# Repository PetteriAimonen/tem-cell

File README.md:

# Custom built TEM cell for EMC measurements

This repository contains FreeCAD and KiCad design files for a [TEM cell](https://en.wikipedia.org/wiki/TEM_cell)
with integrated [LISN](https://en.wikipedia.org/wiki/Line_Impedance_Stabilization_Network).

When combined with a spectrum analyzer, it can be used for EMC pretest measurements.

More construction details are available in [my blog article](http://essentialscrap.com/tem_cell/).

## TEM cell structure

The TEM cell consists of three conductive layers: shield on the top and bottom, and septum in the middle.
The width and spacing of the conductors determines the [characteristic impedance](https://en.wikipedia.org/wiki/Characteristic_impedance) of the transmission line.
The default dimensions are designed for an impedance of 50 ohms, matching most measurement equipment.

Any non-magnetic metal can be used for the construction.
The default thickness of 1.6 mm is set for commonly available PCB material.

Coaxial connectors are mounted at each end of the cell.
In normal operation one end is terminated with a 50 ohm resistor
and the other end is connected to spectrum analyzer or signal generator.

## Dimensions

The classic source for custom TEM cell builds is [Do-it-Yourself Fabrication of an Open TEM Cell for EMC Pre-compliance](http://eagle.chaosproject.com/sandbox/acstrial/newsletters/summer08/pp2.pdf) by Sandeep M. Satav et al, 2008. It provides the formula for characteristic impedance Z0 of the cell. Goal is to select dimensions so that Z0 equals 50 ohms, to facilitate connection to measurement instruments.

$$ Z_0 = \frac{94.15 \Omega}{\sqrt{\epsilon_r} \cdot \left[ \frac{w}{2d(1 - \frac{t}{2d})} + \frac{C_f}{0.0885 \cdot \epsilon_r} \right] } $$

For air as insulator (εr = 1) and thin material (t → 0), this can be simplified to:

$$ Z_0 = \frac{94.15 \Omega}{\frac{w}{2d} + \frac{C_f}{0.0885}} $$

with the parameters:

* **w**: Width of the septum
* **d**: Distance between septum and shield
* **Cf**: Fringe capacitance

The paper further provides value 0.053 pF/cm for the fringe capacitance, based
on earlier paper [Generation of Standard EM Fields Using TEM Transmission Cells](https://www.ieee.li/pdf/essay/generation_of_standard_em_fields_using_tem_transmission_cells.pdf) by Myron L. Crawford, 1974. However Satav's paper describes an open TEM cell (with two walls), while Crawford's paper describes a closed TEM cell (with four walls).

Open TEM cell dimensions calculated based on Cf = 0.053 result in a characteristic impedance 1.7 times higher than expected. Using scale models, I have determined that Cf = 0.03 is closer to the correct value for open TEM cells. Relative width of shields and septum affects this value and also uniformity of the electromagnetic field, but optimal configuration is yet unknown.

## Integrated LISN

[(LISN schematic)](lisn/images/lisn.pdf)

Optionally a LISN can be mounted on the outside of the TEM cell.
This is useful for providing a filtered power supply to the device being tested and for measuring conducted emissions.

The LISN is a nominally 50 µH design loosely following CISPR 16 standard, providing 50 ohm impedance to DUT.
It is suitable for pretesting use for DC-supplied devices with most EMC standards.

The LISN includes integrated DC block and clamping diodes to limit output to ±0.4 Vpk.
Attenuation at the output port is 10 dB.
A slide switch selects between common mode and differential mode measurement.

The LISN maximum current is determined by inductor selection and maximum voltage by capacitor ratings.
With the listed parts, maximum output current is 1.5 A and voltage 100 VDC.

## 3D printed support blocks and LISN enclosure

Correct distance between TEM cell shields and septum is maintained by side support blocks.
These should be printed at a low infill ration (5% recommended) to reduce their effect on the dielectric constant.

LISN enclosure is designed to mount on the tapered section.
Two binding posts go through the shield to provide a connection on the inside of the cell.
Banana jacks and SMA connector are used for connecting a power supply and spectrum analyzer.

## Parametric design

The design in `OpenTEMCell.FCStd` is a [FreeCAD](https://www.freecad.org/) parametric design file.
The critical dimensions can be modified in spreadsheet form and the 3D model will update to match.

One possible design is provided as generated files in subdirectory [Model_L500mm_W350mm_H200mm](Model_L500mm_W350mm_H200mm).

## Part recommendations

Wide variety of materials can be used for the construction.
I have listed below the materials I have used to construct the Model_L500mm_W350mm_H200mm version:

**TEM cell:**

|Item|Count|
|--|--|
| [FR4 PCB material, one sided, 610x457mm](https://www.tme.eu/fi/en/details/lam457x610e1.5/one-layer-laminates/) | 3 pcs |
| [Square flange SMA connector](https://www.tme.eu/fi/en/details/rf2-155-t-00-50-g/sma-smb-smc-connectors/adam-tech/) | 2 pcs |
| [SMA terminator](https://www.tme.eu/fi/en/details/132360/sma-smb-smc-connectors/amphenol-rf/) | 1 pcs |

**LISN:**

|Item|Count|
|--|--|
|Binding posts [CL1572](https://www.tme.eu/en/details/cl1572/4mm-banana-sockets/cliff/) (red) and [CL1575](https://www.tme.eu/en/details/cl1575/4mm-banana-sockets/cliff/) (black) | 2 pcs total |
| Banana connectors [108-0902-001](https://www.digikey.fi/en/products/detail/cinch-connectivity-solutions-johnson/108-0902-001/5929) (red) and [108-0903-001](https://www.digikey.fi/en/products/detail/cinch-connectivity-solutions-johnson/108-0903-001/5930) (black) | 2 pcs total |
| [SMA connector, edge mount](https://www.tme.eu/en/details/rf2145at1750ghdw/sma-smb-smc-connectors/adam-tech/rf2-145a-t-17-50-g-hdw/) | 1 pcs |
| [9 mm long M3 standoffs](https://www.tme.eu/en/details/tff-m3x9_dr113/metal-spacers/dremec/113x09/) | 2 pcs |
| [5 mm long M3 standoffs](https://www.tme.eu/en/details/tfm-m3x5_dr223/metal-spacers/dremec/223x05/) | 2 pcs |
| M3 countersunk screws | 2 pcs |
| [Parts listed in PCB BOM](lisn/gerbers/lisn-BOM.csv) | |

## Correlation to far-field measurements

[Spreadsheet](Model_L500mm_W350mm_H200mm/CorrectionFactors.ods) is provided for calculating correction factor for converting TEM cell measurements in dBµV to far field measurements in dBµV/m. The correction factor depends on frequency.

The values are used in place of antenna factor: they simply added to the dBµV reading of the spectrum analyzer at each frequency. The calculation is based on formula:

$$ 20 \cdot \log_{10}\left[ \frac{η_0 \cdot h}{Z_0 \cdot λ \cdot r} \right] $$

with the parameters:

* η0: [free space impedance](https://en.wikipedia.org/wiki/Impedance_of_free_space) 377 Ω
* Z0: TEM cell characteristic impedance 50 Ω
* h: TEM cell vertical distance between septum and shield (0.1 m for example design)
* r: Far-field measurement distance (3 m for most EMC standards)
* λ: Wavelength of the frequency (λ = c / f)

The formula is based on [Antenna Gain-Factor Equivalent for TEM Cells](https://tsapps.nist.gov/publication/get_pdf.cfm?pub_id=31708) by Perry F. Wilson, 2004.
Ideal isotropic [antenna factor](https://en.wikipedia.org/wiki/Antenna_factor) is used as the equivalent far field measurement antenna for converting into field strength units.

**NOTE: This application of the formula is my own interpretation of the source material.
It may be entirely incorrect. In any case, significant uncertainty remains because DUT geometry affects how effectively fields couple into TEM cell vs. into far field radiation.**

## TinySA Ultra configuration

[Preset configuration file](Model_L500mm_W350mm_H200mm/TinySAUltra_Preset.prs) is provided for [TinySA Ultra](https://www.tinysa.org/) to simplify measurements.

When applied, the preset configures green trace as correction factor table and subtracts it from the measurement traces. Output readings will approximate dBµV/m. Yellow trace is live measurement and purple trace is maximum level hold. Red trace is example of typical radiated emission limits, actual values will depend on applicable standard.

The spectrum analyzer settings used do not match any of the established EMC standards.
To achieve high scanning speed, a large resolution bandwidth and small dwell time of about 0.2 ms is used.
The detector is closest to average measurement type, though the maximum hold will retain the peak value if it hits the dwell time window.
These limitations will result in significant inaccuracies when measuring narrow-band or pulsed emissions.

Signal coupling in TEM cell will depend both on the magnetic and electric field orientations.
One technique is to rotate the DUT into different orientations and let the maximum hold capture the largest emissions. At the end, power down DUT so that you can compare background noise against any spikes from the device.

## License

All the design materials are available under CC-BY-4.0 license.
Preferred attribution:

> © 2023 Petteri Aimonen. Licensed under CC-BY-4.0. https://essentialscrap.com/

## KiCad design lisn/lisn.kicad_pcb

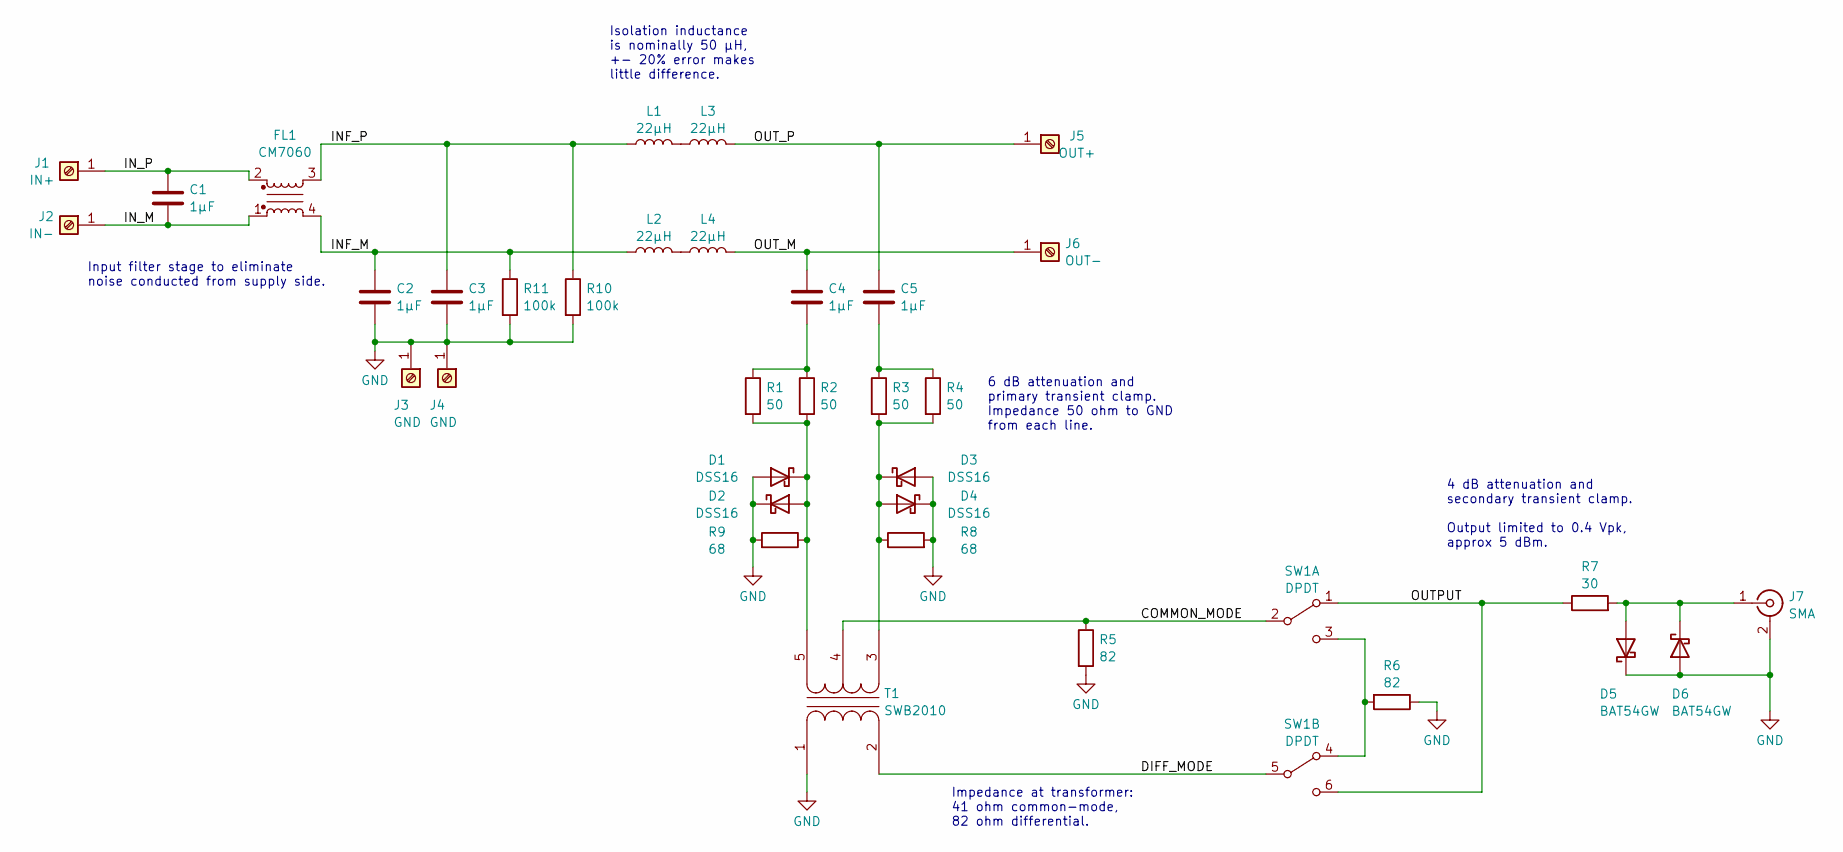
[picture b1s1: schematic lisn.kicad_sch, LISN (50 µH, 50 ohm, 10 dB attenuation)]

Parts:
C1, C2, C3, C4, C5: 1µF; C_1210_3225Metric; PartNumber C1210J105K1RAC7800
D1, D2, D3, D4: DSS16; D_SOD-123; PartNumber DSS16U
D5, D6: BAT54GW; D_SOD-123; PartNumber BAT54GW
FL1: CM7060; L_CommonModeChoke_TDK_ACM7060; PartNumber CM7060M132R-10
J1: IN+; BANANA_JACK_108-0902-001; PartNumber 108-0902-001
J2: IN-; BANANA_JACK_108-0902-001; PartNumber 108-0902-001
J3, J4: GND; MountingHole_3.2mm_M3_Pad
J5: OUT+; MountingHole_3.7mm_Pad; PartNumber CL1572
J6: OUT-; MountingHole_3.7mm_Pad; PartNumber CL1575
J7: SMA; SMA_Amphenol_132289_EdgeMount; PartNumber RF2-145A-T-17-50-G-HDW
L1, L2, L3, L4: 22µH; L_Bourns-SRN8040_8x8.15mm; PartNumber SDR0805-220ML
R1, R2, R3, R4: 50; R_0603_1608Metric
R5, R6: 82; R_0603_1608Metric
R7: 30; R_0603_1608Metric
R8, R9: 68; R_0603_1608Metric
R10, R11: 100k; R_0603_1608Metric
SW1: DPDT; SW_DPDT_CK_JS202011JCQN; PartNumber JS202011JCQN
T1: SWB2010; SWB2010-SMLD; PartNumber SWB2010-SMLD

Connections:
/COMMON_MODE: R5.1, SW1.2 (B), T1.4 (SC)
/DIFF_MODE: SW1.5 (B), T1.2 (AB)
/INF_M: C2.1, FL1.4, L2.1, R11.1
/INF_P: C3.1, FL1.3, L1.1, R10.1
/IN_M: C1.2, FL1.1, J2.1
/IN_P: C1.1, FL1.2, J1.1
/OUTPUT: R7.1, SW1.1 (A), SW1.6 (C)
/OUT_M: C4.1, J6.1, L4.2
/OUT_P: C5.1, J5.1, L3.2
GND: C2.2, C3.2, D1.2 (A), D2.1 (K), D3.2 (A), D4.1 (K), D5.1 (K), D6.2 (A), J3.1, J4.1, J7.2 (Ext), R5.2, R6.1, R8.2, R9.2, R10.2, R11.2, T1.1 (AA)
unnamed: C4.2, R1.1, R2.1
unnamed: C5.2, R3.1, R4.1
unnamed: D1.1 (K), D2.2 (A), R1.2, R2.2, R9.1, T1.5 (SB)
unnamed: D3.1 (K), D4.2 (A), R3.2, R4.2, R8.1, T1.3 (SA)
unnamed: D5.2 (A), D6.1 (K), J7.1 (In), R7.2
unnamed: L1.2, L3.1
unnamed: L2.2, L4.1
unnamed: R6.2, SW1.3 (C), SW1.4 (A)

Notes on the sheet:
Impedance at transformer: 41 ohm common-mode, 82 ohm differential.
4 dB attenuation and secondary transient clamp. Output limited to 0.4 Vpk, approx 5 dBm.
6 dB attenuation and primary transient clamp. Impedance 50 ohm to GND from each line.
Input filter stage to eliminate noise conducted from supply side.
Isolation inductance is nominally 50 µH, +- 20% error makes little difference.

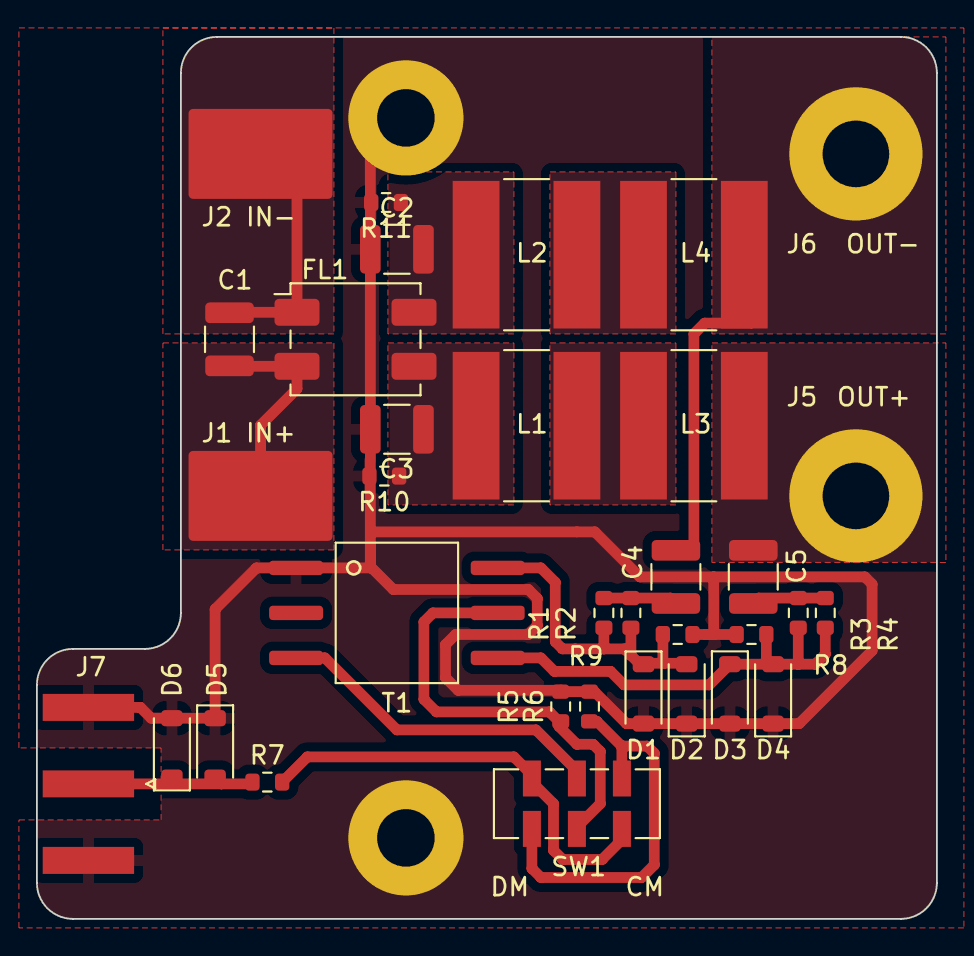
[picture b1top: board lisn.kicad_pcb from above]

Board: 2 copper layers, 50.0 x 49.0 mm, 36 parts (0 on the bottom side), 18 nets.

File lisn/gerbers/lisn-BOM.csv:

"Reference","Value","Footprint","Notes","PartNumber","Qty"
"C1-C5","1µF","Capacitor_SMD:C_1210_3225Metric","100 V 1µF 1210 X7R ceramic capacitor","C1210J105K1RAC7800","5"
"D1-D4","DSS16","Diode_SMD:D_SOD-123","SOD123 schottky diode, > 2A pulse current capability","DSS16U","4"
"D5, D6","BAT54GW","Diode_SMD:D_SOD-123","SOD123 schottky diode, low forward voltage","BAT54GW","2"
"FL1","CM7060","Inductor_SMD:L_CommonModeChoke_TDK_ACM7060","Common mode choke","CM7060M132R-10","1"
"J1","IN+","footprints:BANANA_JACK_108-0902-001","Banana connector, soldered to PCB and screwed into enclosure","108-0902-001","1"
"J2","IN-","footprints:BANANA_JACK_108-0902-001","Banana connector, soldered to PCB and screwed into enclosure","108-0902-001","1"
"J3, J4","GND","MountingHole:MountingHole_3.2mm_M3_Pad","Mounting screws and ground connection","","2"
"J5","OUT+","MountingHole:MountingHole_3.7mm_Pad","Binding post for power output","CL1572","1"
"J6","OUT-","MountingHole:MountingHole_3.7mm_Pad","Binding post for power output","CL1575","1"
"J7","SMA","Connector_Coaxial:SMA_Amphenol_132289_EdgeMount","Edge mount SMA connector","RF2-145A-T-17-50-G-HDW","1"
"L1-L4","22µH","Inductor_SMD:L_Bourns-SRN8040_8x8.15mm","22µH to 27µH inductor, high saturation current","SDR0805-220ML","4"
"R1-R4","50","Resistor_SMD:R_0603_1608Metric","Generic 0603 1% resistor","","4"
"R5, R6","82","Resistor_SMD:R_0603_1608Metric","Generic 0603 1% resistor","","2"
"R7","30","Resistor_SMD:R_0603_1608Metric","Generic 0603 1% resistor","","1"
"R8, R9","68","Resistor_SMD:R_0603_1608Metric","Generic 0603 1% resistor","","2"
"R10, R11","100k","Resistor_SMD:R_0603_1608Metric","Generic 0603 1% resistor","","2"
"SW1","DPDT","footprints:SW_DPDT_CK_JS202011JCQN","Slide switch for output mode selection","JS202011JCQN","1"
"T1","SWB2010","footprints:SWB2010-SMLD","SWB1010-SMLD and SWB3010-SMLD are compatible","SWB2010-SMLD","1"

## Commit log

2023-10-14 Initial design
2023-10-20 Add LISN PCB and enclosure
2023-10-21 Enclosure lid small changes
2023-10-21 Update LISN PCB
2023-10-31 Add parametric FreeCAD design, add README.
2023-10-31 Better clearance for installing LISN mode switch slider
2023-10-31 Add note about dimensions
2023-10-31 Add blog link
2023-10-31 Add license
2023-10-31 Fix broken link
2024-09-24 Add asymmetric TEM cell design file
